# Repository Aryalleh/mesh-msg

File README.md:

# Mava (mesh-msg)

English | [فارسی](README.fa.md)

An off-grid, censorship-resistant messenger built as a **mesh of meshes**.

Messages travel over whatever path exists:

| Tier | Transport | Range | Payload |
|---|---|---|---|
| 0 — Local | BLE, Wi-Fi Direct, Wi-Fi Aware (phone ↔ phone) | 10–100 m per hop | Text + small media |
| 1 — LoRa | LoRa nodes **broadcast**: gateway nodes take packets from a relay and broadcast them to every node in range — offline users, or other relays with no connection to the origin | 2–15 km per hop | Text only (~200 B packets) |
| 2a — Regional | Phones/PCs on a country's domestic network → in-region relay | One country, even during an international blackout | Anything |
| 2b — Global | Federated relays (EU, US, Asia, AU); regions joined by volunteer **bridges** (VPN, Starlink, unfiltered SIM) | Global | Anything |

Chats are one-to-one, **private groups** (a member list: each message goes to every member separately, with ✓✓ per member), **regional public chats**
(one per city or country name, e.g. `#tehran`) and one **global public chat** (`#global`).
All of them travel over every tier above (the global chat skips LoRa to save airtime).

Any phone or PC that can reach a relay can register as a **gateway** ("I'm online — send me
traffic for the mesh around me"). Clients: Android, and desktop (Linux first, then Windows
and macOS).

The relay list updates itself: apps ship the official list ([network/relays.json](network/relays.json),
starting with the original relay eu-1), refresh it, learn relays from other relays, and pass the
relay they use to nearby phones, PCs and LoRa nodes, so a new relay spreads through the mesh even
where the old one is blocked. Each relay is checked before use.

```
   City A                          ~10 km                         City B
 ┌──────────────────┐                                    ┌──────────────────┐
 │ 📱──BLE──📱──📱   │      LoRa backbone (rooftops)      │   📱──📱──BLE──📱 │
 │      📱──BLE──📡──┼────────────────────────────────────┼──📡──BLE──📱      │
 │  (has VPN) 📱     │                                    │     📱 (online)   │
 └───────┼──────────┘                                    └───────┼──────────┘
         └──────────── Internet relay servers (Tier 2) ──────────┘
```

## Core principles

- **Delay-tolerant / store-and-forward** — nodes hold encrypted messages until a better route appears.
- **Identity = public key** — no phone numbers, no accounts.
- **End-to-end encryption above every transport** — relays, LoRa nodes and servers carry only ciphertext. No custom crypto.
- **Transport-agnostic routing** — each tier is just an interface; pick the cheapest one that works.
- **Survives server loss** — Tier 2 is optional; Tiers 0 and 1 work without any internet.
- **Photos, voice and video messages, files** — sent apart from messages so chats never lag: phone to phone over Bluetooth/Wi-Fi/direct internet links (both online). Files marked *important* also go through a relay and reach someone who is offline, a few per day per user. Never over LoRa.

## Threat model highlights

Designed with internet shutdowns (e.g. Iran) in mind: radio direction-finding, device seizure,
blocked servers, no app-store access. See [docs/threat-model.md](docs/threat-model.md).

## Design docs

- [Architecture](docs/architecture.md) — tiers, components, message path
- [Protocol](docs/protocol.md) — identity, packet format, encryption, routing
- [Core](docs/core.md) — shared Go core (protocol, crypto, router)
- [Server](docs/server.md) — regional & global relays, gateways, bridges
- [Desktop](docs/desktop.md) — `meshd` client / gateway / bridge (Linux first)
- [Android](docs/android.md) — app, phone-to-phone mesh
- [Firmware](docs/firmware.md) — LoRa node hardware framework
- [Threat model](docs/threat-model.md)
- [Decisions](docs/decisions.md) · [Roadmap](docs/roadmap.md)

## Status

M0–M3 implemented: Go core, simulator, relay and Linux desktop (`meshd` + `mesh`),
with language-neutral test vectors. M4 (LoRa firmware): the whole node
(protocol, router, MAC, store, host link) is board-independent and host-tested against the same
vectors (`make -C firmware test`); `scripts/e2e-lora.sh` sends a text PC → node → repeater →
node → PC with real firmware nodes on a simulated radio; PlatformIO builds for Heltec V3,
T-Beam S3, RAK4631 and T-Echo exist but are not yet verified on hardware. M5 (Android): the core is bound with gomobile
(`mobile/`), and `android/` has the app — Compose UI in Persian and English, BLE mesh
transport, USB LoRa link, foreground service — built and tested on the JVM, not yet on phones.
See [roadmap](docs/roadmap.md).

## Layout

```
docs/        design docs
spec/        protocol test vectors
core/        shared Go core: protocol, crypto, router, store, relay client
server/      relay server (Go)
desktop/     meshd daemon + CLI + web UI (Go; Linux first)
android/     Android app (Kotlin + Go core via gomobile)
firmware/    LoRa node firmware (C++ / PlatformIO)
sim/         network simulator (Go, uses core/)
```

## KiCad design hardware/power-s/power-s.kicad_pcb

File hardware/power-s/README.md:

# Model S power board

The power section of the Model S handheld (docs/handheld.md §1–2) as its own 2-layer board
inside the case, plugged into the 2-layer main board. Everything here is **generated**: change
the scripts, not the KiCad files.

| | |
|---|---|
| Size | 54 × 36 mm, 2 layers, 1.6 mm, all parts on top, 4 × M2 holes |
| Input | USB-C (5 V sink, CC 5.1 k, USBLC6 on D+/D−, SMF5.0A on VBUS) |
| Battery | 1-cell LiPo with 10 k NTC on JST-PH 3-pin (1 = BAT+, 2 = NTC, 3 = BAT−) |
| PMU | X-Powers AXP2101: linear charger ≤ 1 A, power path, fuel gauge, DCDC1 + 6 LDOs |
| RTC | NXP PCF85063A from the battery through a TI TPS7A02 (25 nA) |
| To main board | J3, 2 × 14 1.27 mm SMD header (mates with a 2 × 14 1.27 mm SMD socket) |

## Rails

| Rail | Source | Max | Model S load | J3 pins |
|---|---|---|---|---|
| VBAT | battery | – | NS4150B, motor, LTE board (2 A peaks) | 1–4 |
| VSYS | AXP2101 power path | 2 A total | spare for loads that must run from USB without a battery | 7–8 |
| +3V3 | DCDC1 | 2 A | ESP32-S3, flash, PSRAM | 11–13 |
| 3V3_LORA | ALDO2 | 300 mA | SX1262 module | 15 |
| 3V3_AUDIO | ALDO3 | 300 mA | ES8388 | 16 |
| 3V3_SD | ALDO4 | 300 mA | microSD | 17 |
| 3V3_LCD | BLDO1 | 300 mA | screen VCI, touch | 18 |
| 3V3_GPS | BLDO2 | 300 mA | GPS / LTE option (J6 VCC, LTE load-switch enable) | 19 |
| VSPARE | ALDO1 | 300 mA | spare, off by default | 20 |
| VRTC | TPS7A02 from VBAT | 200 mA | PCF85063A only | – |

GND on J3 pins 5, 6, 9, 10, 14, 21. Header pins carry 1 A each.

## Signals to the ESP32-S3

| J3 | Net | ESP32-S3 | |
|---|---|---|---|
| 23 / 24 | I2C_SDA / I2C_SCL | GPIO18 / GPIO8 | AXP2101 at 0x34, PCF85063A at 0x51; 2.2 k pull-ups on this board |
| 25 | PMU_IRQ | GPIO2 | open drain, 10 k pull-up here; AXP2101 IRQ and RTC INT wired together |
| 26 | PMU_PWROK | (EN, optional) | high once the rails are up |
| 22 | PWR_KEY | – | side power key on the main board, to GND (parallel to SW1 here) |
| 27 / 28 | USB_D_P / USB_D_N | GPIO20 / GPIO19 | native USB, ESD-protected at the connector |

**Charge status and battery capacity** reach the ESP32-S3 over I2C, nothing else is needed:
the AXP2101's fuel gauge (E-Gauge) gives the state of charge in % (REG A4h), the battery
voltage and charge current from its ADC, and the charger state (charging / full / discharging,
VBUS present) in its status registers. PMU_IRQ goes low on every change (USB in/out, charge
start/done, battery low, power key), so the ESP32-S3 sleeps until something happens.
For an accurate percentage the firmware loads the battery's 128-byte model into the gauge at
start-up (X-Powers design guide §6); without it the gauge uses its generic curve.
XPowersLib (already used in `firmware/`) has the register map.

## Firmware duties

- Set each rail's voltage and enable it before use; rails start from the AXP2101's eFuse
  defaults.
- Charge current ≤ 1 A for the 2500 mAh pack (REG 62h), target 4.2 V (REG 64h).
- TS pin: the pack's 10 k NTC; for a pack without NTC fit R10 (10 k, DNP) or turn TS off.
- PCF85063A: CAP_SEL = 12.5 pF, CLKOUT off (COF = 111).

## Files

| File | |
|---|---|
| `generate_schematic.py` | the schematic (spec + drawing; `verify()` proves they match) |
| `place_board.py` | placement |
| `route_board.py` | routing: power paths scripted, the rest Freerouting, stored in `routing/` |
| `make_rails.py` | power symbols for this board's rails (`lib/rails.kicad_sym`) |
| `lib/` | AXP2101, TPS7A02, PCF85063ATT, inductor: symbols/footprints from LCSC (easyeda2kicad) |
| `kicad-env.sh` | KiCad 10 from the AppImage (`kicad-cli`, `kpy` = KiCad's Python) |
| `schlib.py`, `pcblib.py`, `routelib.py`, `subcircuits.py`, `jlc_cpl.py` | the libraries the scripts use |

Regenerate:

```
. ./kicad-env.sh
python3 make_rails.py
python3 generate_schematic.py --force --render
kpy place_board.py --force
kpy route_board.py
```

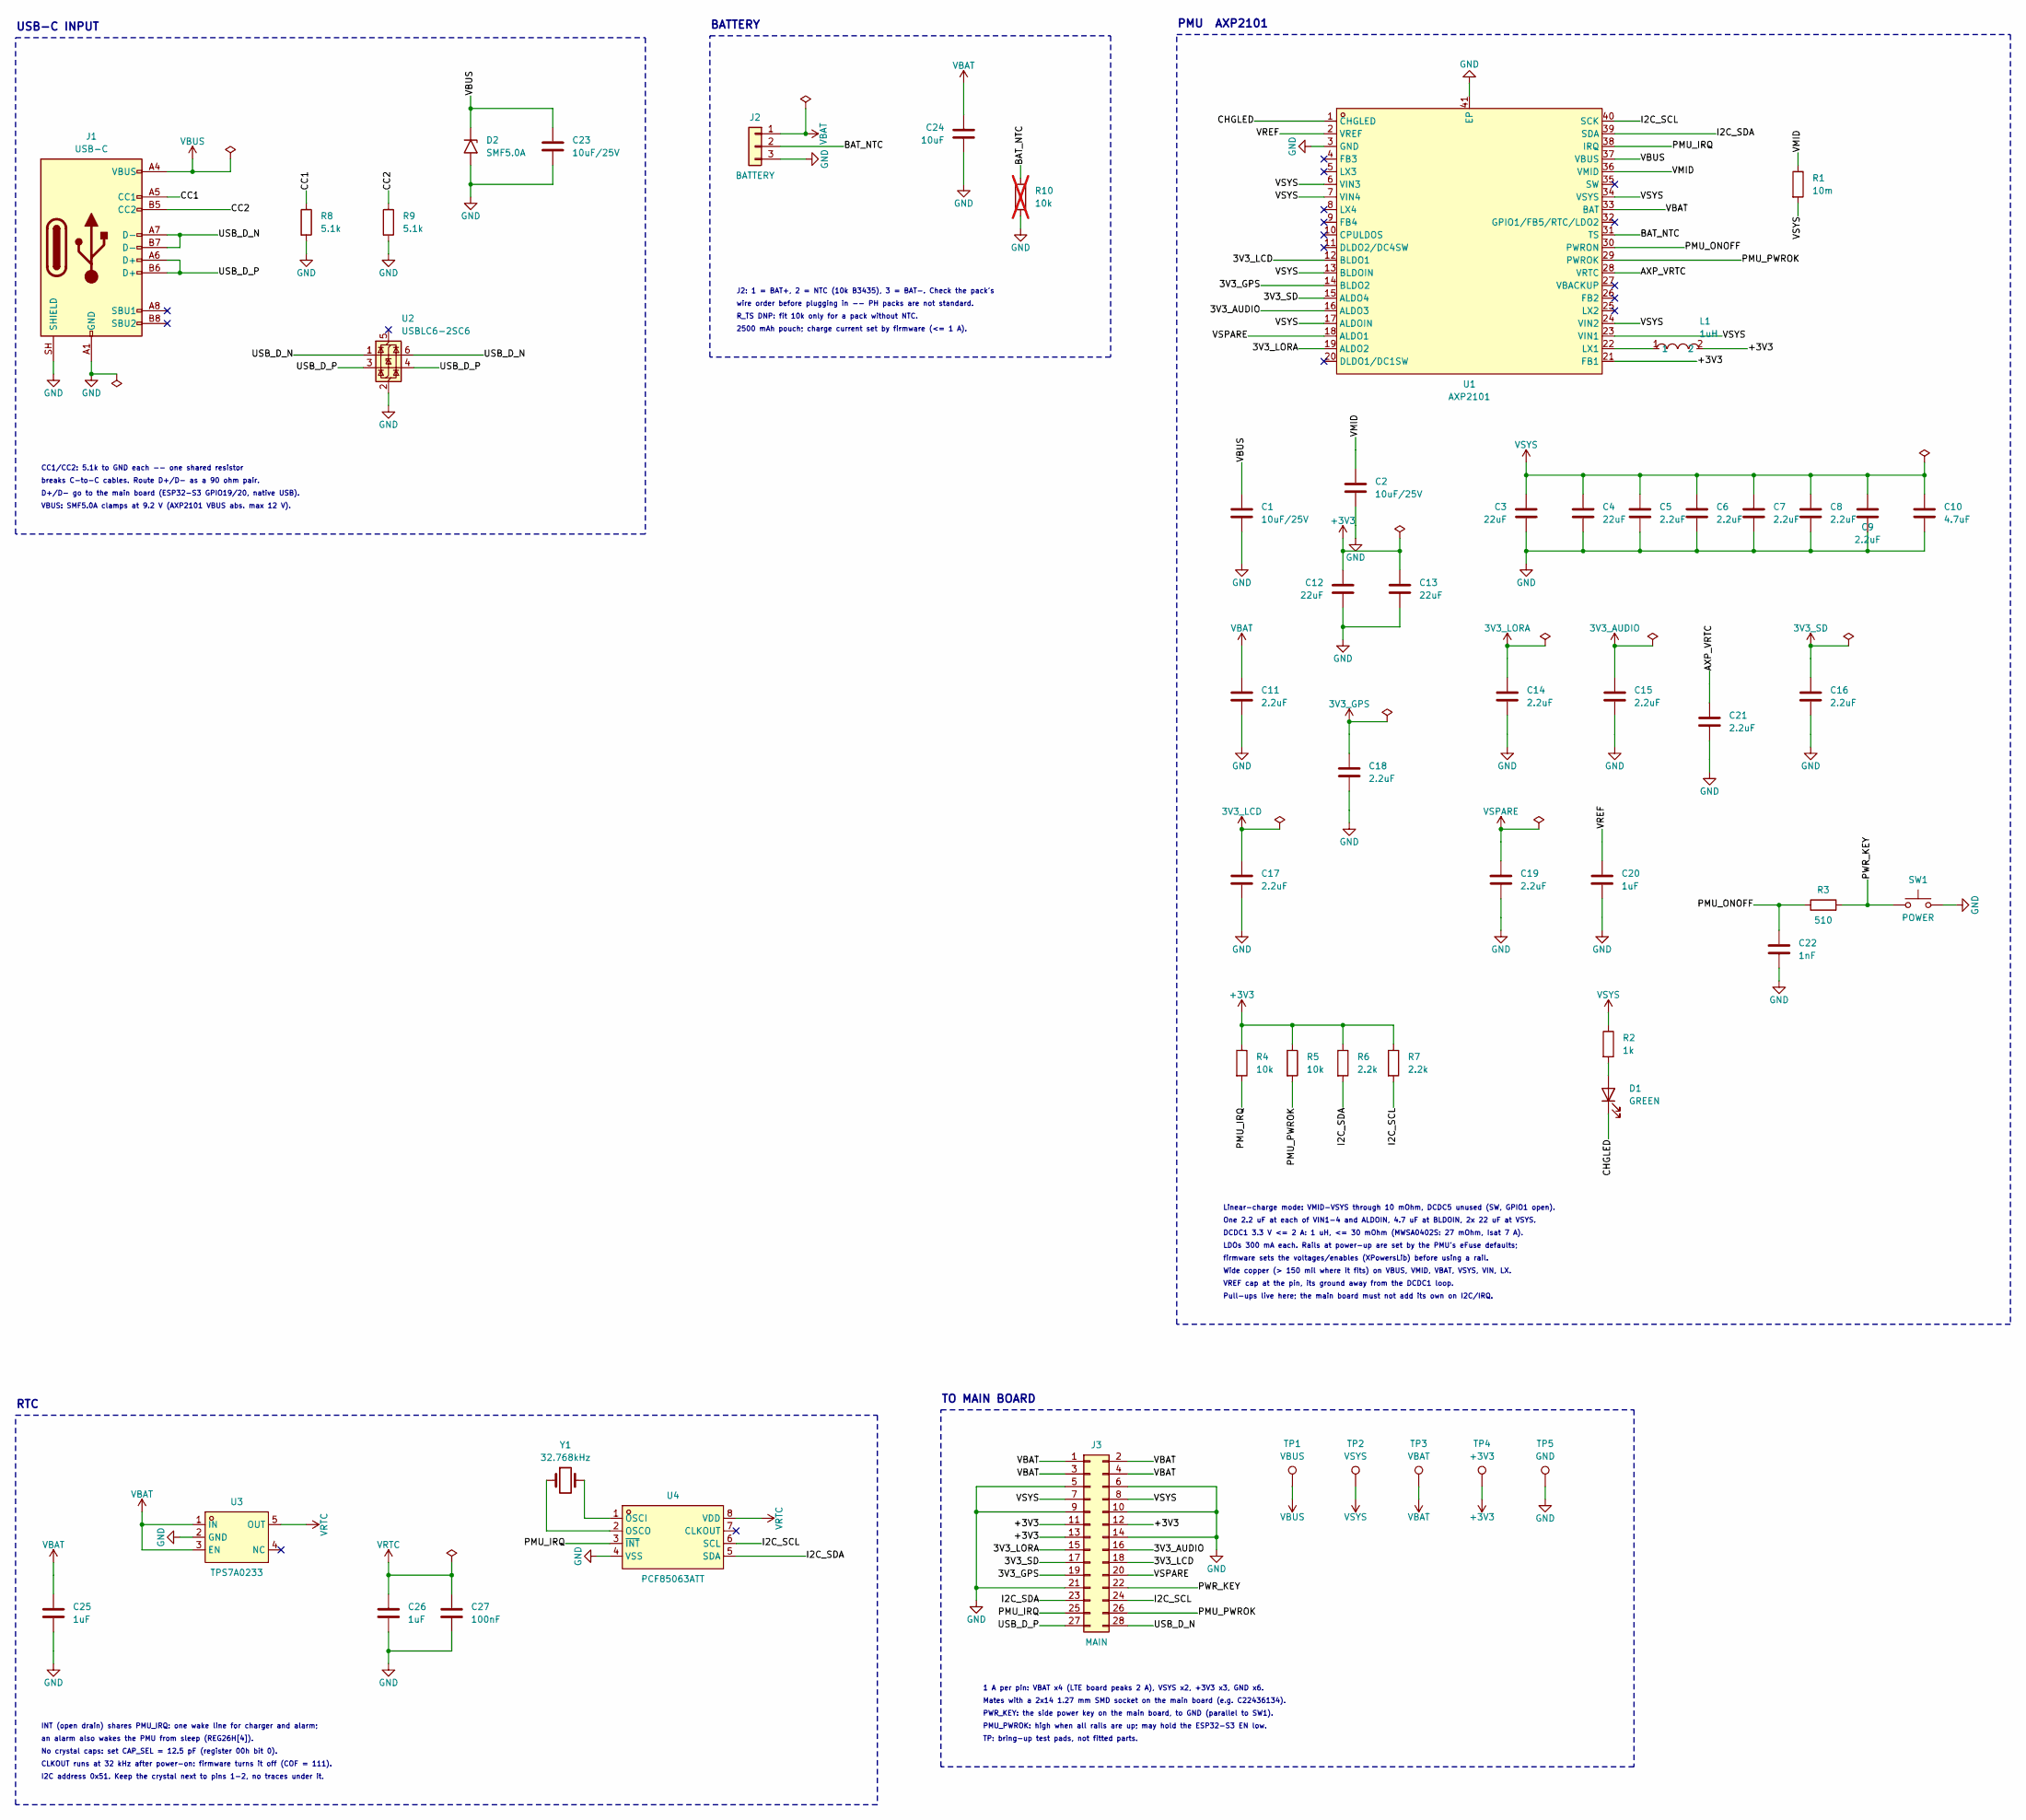
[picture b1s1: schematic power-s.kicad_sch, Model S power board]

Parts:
C1, C2, C23: 10uF/25V; C_0805_2012Metric; MPN CL21A106KAYNNNE; LCSC C15850
C3, C4, C12, C13: 22uF; C_0805_2012Metric; MPN CL21A226MAQNNNE; LCSC C45783
C5, C6, C7, C8, C9, C11, C14, C15, C16, C17, C18, C19, C21: 2.2uF; C_0402_1005Metric; MPN CL05A225MQ5NSNC; LCSC C12530
C10: 4.7uF; C_0603_1608Metric; MPN CL10A475KO8NNNC; LCSC C19666
C20, C25, C26: 1uF; C_0402_1005Metric; MPN CL05A105KA5NQNC; LCSC C52923
C22: 1nF; C_0402_1005Metric; MPN 0402B102K500NT; LCSC C1523
C24: 10uF; C_0603_1608Metric; MPN CL10A106KP8NNNC; LCSC C19702
C27: 100nF; C_0402_1005Metric; MPN CL05B104KO5NNNC; LCSC C1525
D1: GREEN; LED_0603_1608Metric; MPN 19-217/GHC-YR1S2/6T; LCSC C2986059
D2: SMF5.0A; D_SOD-123F; MPN SMF5.0A; LCSC C193402
J1: USB-C; USB_C_Receptacle_HRO_TYPE-C-31-M-12; MPN TYPE-C-31-M-12; LCSC C165948
J2: BATTERY; JST_PH_S3B-PH-SM4-TB_1x03-1MP_P2.00mm_Horizontal; MPN S3B-PH-SM4-TB(LF)(SN); LCSC C265101
J3: MAIN; PinHeader_2x14_P1.27mm_Vertical_SMD; MPN LCK-PH19-12728PC40D55-G1WT0; LCSC C54950782
L1: 1uH; IND-SMD_L4.4-W4.2; MPN MWSA0402S-1R0MT; LCSC C408332
R1: 10m; R_1206_3216Metric; MPN FMF06FTHR010-LH; LCSC C105362
R2: 1k; R_0402_1005Metric; MPN 0402WGF1001TCE; LCSC C11702
R3: 510; R_0402_1005Metric; MPN 0402WGF5100TCE; LCSC C25123
R4, R5: 10k; R_0402_1005Metric; MPN 0402WGF1002TCE; LCSC C25744
R6, R7: 2.2k; R_0402_1005Metric; MPN 0402WGF2201TCE; LCSC C25879
R8, R9: 5.1k; R_0402_1005Metric; MPN 0402WGF5101TCE; LCSC C25905
R10: 10k; R_0402_1005Metric; MPN 0402WGF1002TCE; LCSC C25744; not fitted
SW1: POWER; SW_Push_1P1T_XKB_TS-1187A; MPN TS-1187A-B-A-B; LCSC C318884
TP1: VBUS; TestPoint_Pad_D1.0mm
TP2: VSYS; TestPoint_Pad_D1.0mm
TP3: VBAT; TestPoint_Pad_D1.0mm
TP4: +3V3; TestPoint_Pad_D1.0mm
TP5: GND; TestPoint_Pad_D1.0mm
U1: AXP2101; QFN-40_L5.0-W5.0-P0.40-TL-EP3.4; MPN AXP2101; LCSC C3036461
U2: USBLC6-2SC6; SOT-23-6; MPN USBLC6-2SC6; LCSC C7519
U3: TPS7A0233; SOT-23-5_L2.9-W1.6-P0.95-LS2.8-BR; MPN TPS7A0233PDBVR; LCSC C2887324
U4: PCF85063ATT; TSSOP-8_L3.0-W3.0-P0.65-LS4.9-BL; MPN PCF85063ATT/AJ; LCSC C165608
Y1: 32.768kHz; Crystal_SMD_3215-2Pin_3.2x1.5mm; MPN SC-32S 32.768kHz 20PPM 12.5pF; LCSC C97606

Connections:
/AXP_VRTC: C21.1, U1.28 (VRTC)
/BAT_NTC: J2.2, R10.1, U1.31 (TS)
/CC1: J1.A5 (CC1), R8.1
/CC2: J1.B5 (CC2), R9.1
/CHGLED: D1.1 (K), U1.1 (CHGLED)
/I2C_SCL: J3.24, R7.2, U1.40 (SCK), U4.6 (SCL)
/I2C_SDA: J3.23, R6.2, U1.39 (SDA), U4.5 (SDA)
/PMU_IRQ: J3.25, R4.2, U1.38 (IRQ), U4.3 (~INT)
/PMU_ONOFF: C22.1, R3.1, U1.30 (PWRON)
/PMU_PWROK: J3.26, R5.2, U1.29 (PWROK)
/PWR_KEY: J3.22, R3.2, SW1.1
/USB_D_N: J1.A7 (D-), J1.B7 (D-), J3.28, U2.1 (I/O1), U2.6 (I/O1)
/USB_D_P: J1.A6 (D+), J1.B6 (D+), J3.27, U2.3 (I/O2), U2.4 (I/O2)
/VMID: C2.1, R1.1, U1.36 (VMID)
/VREF: C20.1, U1.2 (VREF)
unnamed: D1.2 (A), R2.2
unnamed: L1.1, U1.22 (LX1)
unnamed: U4.1 (OSCI), Y1.2
unnamed: U4.2 (OSCO), Y1.1

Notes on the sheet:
INT (open drain) shares PMU_IRQ: one wake line for charger and alarm;
RTC
I2C address 0x51. Keep the crystal next to pins 1-2, no traces under it.
Wide copper (> 150 mil where it fits) on VBUS, VMID, VBAT, VSYS, VIN, LX.
TP: bring-up test pads, not fitted parts.
D+/D- go to the main board (ESP32-S3 GPIO19/20, native USB).
wire order before plugging in -- PH packs are not standard.
1 A per pin: VBAT x4 (LTE board peaks 2 A), VSYS x2, +3V3 x3, GND x6.
One 2.2 uF at each of VIN1-4 and ALDOIN, 4.7 uF at BLDOIN, 2x 22 uF at VSYS.
2500 mAh pouch; charge current set by firmware (<= 1 A).
TO MAIN BOARD
J2: 1 = BAT+, 2 = NTC (10k B3435), 3 = BAT-. Check the pack's
VBUS: SMF5.0A clamps at 9.2 V (AXP2101 VBUS abs. max 12 V).
USB-C INPUT
Pull-ups live here; the main board must not add its own on I2C/IRQ.
No crystal caps: set CAP_SEL = 12.5 pF (register 00h bit 0).
PWR_KEY: the side power key on the main board, to GND (parallel to SW1).
VREF cap at the pin, its ground away from the DCDC1 loop.
PMU_PWROK: high when all rails are up; may hold the ESP32-S3 EN low.
LDOs 300 mA each. Rails at power-up are set by the PMU's eFuse defaults;
firmware sets the voltages/enables (XPowersLib) before using a rail.
an alarm also wakes the PMU from sleep (REG26H[4]).
Mates with a 2x14 1.27 mm SMD socket on the main board (e.g. C22436134).
PMU AXP2101
breaks C-to-C cables. Route D+/D- as a 90 ohm pair.
CLKOUT runs at 32 kHz after power-on: firmware turns it off (COF = 111).
CC1/CC2: 5.1k to GND each -- one shared resistor
R_TS DNP: fit 10k only for a pack without NTC.
DCDC1 3.3 V <= 2 A: 1 uH, <= 30 mOhm (MWSA0402S: 27 mOhm, Isat 7 A).
Linear-charge mode: VMID-VSYS through 10 mOhm, DCDC5 unused (SW, GPIO1 open).
BATTERY

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
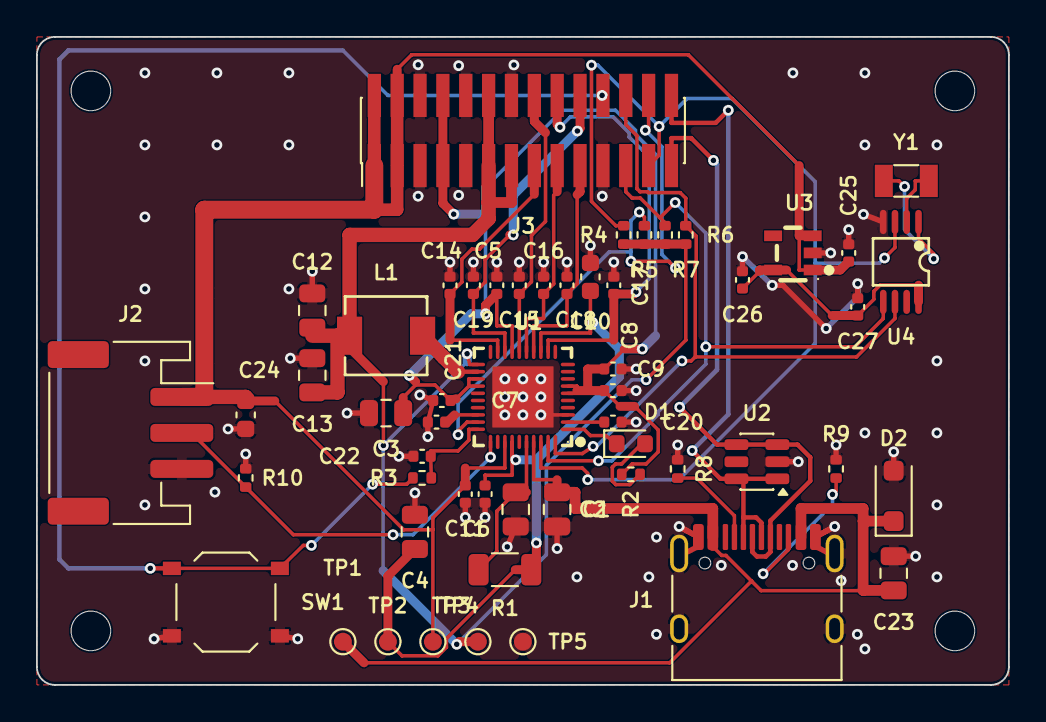
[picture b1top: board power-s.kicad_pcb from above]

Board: 2 copper layers, 54.0 x 36.0 mm, 58 parts (0 on the bottom side), 31 nets.

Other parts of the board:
H1, H2, H3, H4: MountingHole_2.2mm

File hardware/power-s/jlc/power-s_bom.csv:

Comment,Designator,Footprint,LCSC
10uF/25V,"C1,C2,C23",C_0805_2012Metric,C15850
4.7uF,C10,C_0603_1608Metric,C19666
1uF,"C20,C25,C26",C_0402_1005Metric,C52923
1nF,C22,C_0402_1005Metric,C1523
10uF,C24,C_0603_1608Metric,C19702
100nF,C27,C_0402_1005Metric,C1525
22uF,"C3,C4,C12,C13",C_0805_2012Metric,C45783
2.2uF,"C5,C6,C7,C8,C9,C11,C14,C15,C16,C17,C18,C19,C21",C_0402_1005Metric,C12530
GREEN,D1,LED_0603_1608Metric,C2986059
SMF5.0A,D2,D_SOD-123F,C193402
USB-C,J1,USB_C_Receptacle_HRO_TYPE-C-31-M-12,C165948
BATTERY,J2,JST_PH_S3B-PH-SM4-TB_1x03-1MP_P2.00mm_Horizontal,C265101
MAIN,J3,PinHeader_2x14_P1.27mm_Vertical_SMD,C54950782
1uH,L1,IND-SMD_L4.4-W4.2,C408332
10m,R1,R_1206_3216Metric,C105362
1k,R2,R_0402_1005Metric,C11702
510,R3,R_0402_1005Metric,C25123
10k,"R4,R5",R_0402_1005Metric,C25744
2.2k,"R6,R7",R_0402_1005Metric,C25879
5.1k,"R8,R9",R_0402_1005Metric,C25905
POWER,SW1,SW_Push_1P1T_XKB_TS-1187A,C318884
AXP2101,U1,QFN-40_L5.0-W5.0-P0.40-TL-EP3.4,C3036461
USBLC6-2SC6,U2,SOT-23-6,C7519
TPS7A0233,U3,SOT-23-5_L2.9-W1.6-P0.95-LS2.8-BR,C2887324
PCF85063ATT,U4,TSSOP-8_L3.0-W3.0-P0.65-LS4.9-BL,C165608
32.768kHz,Y1,Crystal_SMD_3215-2Pin_3.2x1.5mm,C97606

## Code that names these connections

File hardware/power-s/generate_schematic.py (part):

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  + 6 LDOs for the Model S rails) -> 2x14 1.27 mm board-to-board header to the
  main board. RTC (PCF85063A) on the battery through a 25 nA LDO (TPS7A02).
  Charge state reaches the ESP32-S3 over I2C (AXP2101 status/fuel-gauge
  registers) and PMU_IRQ (GPIO2), which fires on every charger event.

AXP2101 circuit = X-Powers "AXP2101 design guide V1.0" §3.2 (linear-charge
mode) and datasheet V1.4 table 4-1; pin numbers checked against both.
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        self.put(s, self.j, x, y, mirror="y")
        p1, p2, p3 = (s.pin(self.j, n) for n in ("1", "2", "3"))
        s.stub(self.j, "1", 5.08, power="rails:VBAT")
        s.stub(self.j, "2", 12.7, label="BAT_NTC")
        g = s.stub(self.j, "3", 5.08, power="GND")
        # PWR_FLAG: VBAT and the battery's GND enter the board here
        top = (p1[0] + 5.08, p1[1])
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                    place=lambda r, xx, yy: self.put(s, r, xx, yy))
        self.put(s, self.rts, snap(x + 22.86), snap(y + 10.16))
        s._sym(self.rts)[0]["dnp"] = True
        s.stub(self.rts, 1, 2.54, label="BAT_NTC")
        s.stub(self.rts, 2, 2.54, power="GND")


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            self.banks.append((rail, refs_, kind))

        bank("VBUS", ["10uF/25V"])
        bank("VMID", ["10uF/25V"], "label")
        bank("VSYS", ["22uF", "22uF", "2.2uF", "2.2uF", "2.2uF", "2.2uF", "2.2uF", "4.7uF"])
        bank("VBAT", ["2.2uF"])
        bank("+3V3", ["22uF", "22uF"])
        for rail in ("3V3_LORA", "3V3_AUDIO", "3V3_SD", "3V3_LCD", "3V3_GPS", "VSPARE"):
            bank(rail, ["2.2uF"])
        bank("VREF", ["1uF"], "label")
        bank("AXP_VRTC", ["2.2uF"], "label")

        # charge LED: VSYS -> 1k -> LED -> CHGLED (guide §4.3 item 2)
        self.rled = P("R", RES["1k"])
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            self.pull.append(r)

        self.notes = [
            "Linear-charge mode: VMID-VSYS through 10 mOhm, DCDC5 unused (SW, GPIO1 open).",
            "One 2.2 uF at each of VIN1-4 and ALDOIN, 4.7 uF at BLDOIN, 2x 22 uF at VSYS.",
            "DCDC1 3.3 V <= 2 A: 1 uH, <= 30 mOhm (MWSA0402S: 27 mOhm, Isat 7 A).",
            "LDOs 300 mA each. Rails at power-up are set by the PMU's eFuse defaults;",
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        # VMID -> 10 mOhm -> VSYS, beside the right flank
        rx, ry = snap(x + 58.42), snap(y - 10.16)
        self.put(s, self.rmid, rx, ry)
        s.stub(self.rmid, 1, 2.54, label="VMID")
        s.stub(self.rmid, 2, 2.54, label="VSYS")

        # capacitor banks in rows below the IC
        bx0, by = snap(x - 45.72), snap(y + 45.72)
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        s.stub(self.rled, 1, 2.54, power="rails:VSYS")
        self.put(s, self.led, lx0, snap(py + 10.16), rot=90)
        s.wire(s.pin(self.rled, 2), s.pin(self.led, 2))
        s.stub(self.led, 1, 5.08, label="CHGLED")

        # power key: PWRON label, 1nF down to GND, 510R across to PWR_KEY, key to GND
        kx = snap(bx0 + 81.28)
        self.put(s, self.ckey, kx, snap(py + 7.62))
        s.stub(self.ckey, 2, 2.54, power="GND")
        top = s.pin(self.ckey, 1)
        n = (top[0], snap(top[1] - 5.08))                  # PMU_ONOFF node
        s.wire(top, n, (n[0] - 5.08, n[1]))
        s.label("PMU_ONOFF", n[0] - 5.08, n[1], angle=180)
        # 510R horizontal, pin 1 on the left (rot 90 turns pin 1 to the left)
        self.put_pin(s, self.rkey, 1, (snap(n[0] + 5.08), n[1]), rot=90)
        s.wire(n, s.pin(self.rkey, 1))
        k = (snap(s.pin(self.rkey, 2)[0] + 5.08), n[1])    # PWR_KEY node
        s.wire(s.pin(self.rkey, 2), k)
        s.wire(k, (k[0], snap(k[1] - 5.08)))
        s.label("PWR_KEY", k[0], snap(k[1] - 5.08), angle=90)
        self.put_pin(s, self.sw, 1, (snap(k[0] + 5.08), k[1]))
        s.wire(k, s.pin(self.sw, 1))
        s.stub(self.sw, 2, 2.54, power="GND")
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        self.put(s, r, snap(x + 76.2), y)
        s.stub(r, "8", 5.08, power="rails:VRTC")
        s.stub(r, "4", 2.54, power="GND")
        s.stub(r, "3", 5.08, label="PMU_IRQ")
        s.stub(r, "5", 5.08, label="I2C_SDA")
        s.stub(r, "6", 5.08, label="I2C_SCL")
        s.nc(r, "7")
        # crystal above-left of the RTC: OSCI and OSCO each one clean L, no crossing
        o1, o2 = s.pin(r, "1"), s.pin(r, "2")
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                                  "", "", ""))
            self.conn(net, (tp, 1))
            self.tps.append((tp, net))
        self.notes = ["1 A per pin: VBAT x4 (LTE board peaks 2 A), VSYS x2, +3V3 x3, GND x6.",
                      "Mates with a 2x14 1.27 mm SMD socket on the main board (e.g. C22436134).",
                      "PWR_KEY: the side power key on the main board, to GND (parallel to SW1).",
                      "PMU_PWROK: high when all rails are up; may hold the ESP32-S3 EN low.",
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
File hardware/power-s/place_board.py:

"""Model S power board -- placement.

    . ./kicad-env.sh && kpy place_board.py [--force]

Board mm, origin top-left, Y down. Re-running resets every part listed here
to its table position (parts locked in KiCad are not touched by this script
only if you remove them from the table first).

Mechanics (README.md): 54 x 36 mm, 2 layers, all parts on top. Top edge faces
the main board (2x14 1.27 mm header J3, mezzanine), USB-C on the bottom edge,
battery JST-PH on the left edge, 4x M2 holes in the corners.
"""
import os
import sys

HERE = os.path.dirname(os.path.abspath(__file__))
sys.path.insert(0, HERE)
import pcblib                                     # noqa: E402
from pcblib import Board                          # noqa: E402

NAME = "power-s"
W, H = 54.0, 36.0          # case inside is ~58 mm wide (docs/handheld.md: 62 mm outside)

# Pad orientation used below: a two-pad part at rot 0 has pad 1 on the left,
# rot 90 pad 1 at the bottom, rot 180 on the right, rot 270 at the top.
# Every capacitor's pad 1 is its rail, pad 2 ground, so the rot puts the rail
# pad toward the pin it serves.
#
# AXP2101 rotated 180 deg (pad positions at (27, 20)):
#   top    y 17.5  LDO outputs and their inputs, pins 19..12 at x 25.6..28.4
#   left   x 24.5  FB1 18.2, LX1 18.6, VIN1/2 19.0/19.4, VRTC 21.0, PWROK 21.4, PWRON 21.8
#   bottom y 22.5  TS 25.2, BAT 26.0, VSYS 26.4, VMID 27.2, VBUS 27.6, IRQ/SDA/SCL 28.0..28.8
#   right  x 29.5  VIN3/4 19.4/19.8, GND 21.0, VREF 21.4, CHGLED 21.8
U1 = (27.0, 20.0)

PLACEMENT = {
    # ref: (x, y, rot)
    "U1": (U1[0], U1[1], 180),
    "J3": (27.0, 5.2, 90),            # to the main board, along the top edge
    # DCDC1: LX1 -> L1 -> +3V3, output caps beside L1, VIN1/2 caps under it
    "L1": (19.4, 16.6, 0),            # pad 1 (LX) on the right, facing pin 22
    "C12": (15.3, 15.2, 90),
    "C13": (15.3, 18.8, 90),
    "C7": (22.5, 20.2, 180),          # VIN1/2 2.2 uF at the pins
    "C3": (19.4, 20.9, 180),          # VIN1/2 22 uF
    "C21": (22.2, 21.4, 180),         # VRTC (pin 28)
    "C22": (21.4, 23.3, 180),           # PWRON 1 nF
    "R3": (21.4, 24.5, 180),            # PWRON 510 R to the key
    # top row: LDO outputs and ALDOIN/BLDOIN, in pin order, rail pad down, 1.3 mm pitch:
    # route_board.py fans the 0.4 mm pins out to them in a staircase
    "C14": (22.95, 13.8, 90),          # 3V3_LORA   pin 19
    "C19": (24.25, 13.8, 90),          # VSPARE     pin 18
    "C5": (25.55, 13.8, 90),           # ALDOIN     pin 17
    "C15": (26.8, 13.8, 90),          # 3V3_AUDIO  pin 16
    "C16": (28.15, 13.8, 90),          # 3V3_SD     pin 15
    "C18": (29.45, 13.8, 90),          # 3V3_GPS    pin 14
    "C10": (30.75, 13.335, 90),          # BLDOIN 4.7 uF pin 13
    "C17": (32.05, 13.8, 90),         # 3V3_LCD    pin 12
    # right: VIN3/4, VREF, charge LED
    "C9": (32.0, 18.45, 0),
    "C8": (32.0, 19.65, 0),
    "C20": (32.0, 21.4, 0),          # VREF 1 uF at the pin
    "D1": (33.0, 22.6, 0),            # CHGLED sinks: cathode (pad 1) toward U1
    "R2": (33.0, 24.3, 0),
    # bottom: BAT, VSYS, VMID, VBUS, the 10 mOhm VMID->VSYS link, VSYS bulk
    "C11": (23.8, 25.4, 270),         # BAT 2.2 uF
    "C6": (24.9, 25.4, 270),          # VSYS 2.2 uF pin 34
    "C2": (26.6, 26.25, 270),         # VMID 10 uF
    "C1": (28.9, 26.25, 270),         # VBUS 10 uF (I2C leaves above it)
    "R1": (26.0, 29.6, 0),
    "C4": (21.0, 27.5, 90),           # VSYS 22 uF bulk
    # I2C / IRQ / PWROK pull-ups to +3V3, under the header's signal pins
    "R4": (32.6, 11.0, 90),
    "R5": (33.75, 11.0, 90),
    "R6": (34.9, 11.0, 90),
    "R7": (36.05, 11.0, 90),
    # USB-C on the bottom edge, right: D+/D- run up the free right side to
    # J3 27/28; ESD flow-through right above the receptacle
    "J1": (40.0, H - 4.17, 0),
    "U2": (40.0, 23.6, 180),
    "R8": (35.6, 24.0, 90),
    "R9": (44.4, 24.0, 90),
    "D2": (47.6, 25.5, 90),
    "C23": (47.6, 29.8, 90),
    # battery on the left edge, cable leaves to the left; VBAT is one short
    # run to J3 pins 1-4 (the header's left end) and to BAT (pin 33)
    "J2": (5.2, 22.0, 270),
    "C24": (11.6, 21.0, 270),         # VBAT pad up, in line with J2 pin 1
    "R10": (11.6, 24.5, 90),
    # RTC, top right
    "U3": (42.0, 12.0, 0),
    "C25": (45.1, 12.0, 90),
    "C26": (39.2, 13.5, 90),
    "U4": (48.0, 12.5, 180),
    "Y1": (48.3, 8.0, 0),
    "C27": (45.6, 15.0, 90),
    # power key (bench; the case key is on the main board, PWR_KEY on J3)
    "SW1": (10.5, 31.4, 0),
    # test pads along the bottom edge
    "TP1": (17.0, 33.6, 0),
    "TP2": (19.5, 33.6, 0),
    "TP3": (22.0, 33.6, 0),
    "TP4": (24.5, 33.6, 0),
    "TP5": (27.0, 33.6, 0),
}
HOLES = [(3.0, 3.0), (W - 3.0, 3.0), (3.0, H - 3.0), (W - 3.0, H - 3.0)]


def main():
    pcblib.create_board(__file__, NAME, layers=2)
    b = Board(__file__, NAME, size=(W, H))
    b.sync_footprints(prune=True)
    b.refresh_footprints()                          # pick up lib/ fixes (fix_footprints.py)
    b.outline(radius=1.0)
    b.place_all(PLACEMENT)
    b.link_schematic()
    # match the symbols: test pads on the BOM (no LCSC, so not on the JLC BOM), R10 not fitted
    for ref, fp in b.fps.items():
        if ref.startswith("TP"):
            fp.SetExcludedFromBOM(False)    # symbols are on the BOM; jlc_cpl skips parts without LCSC
    b.fps["R10"].SetDNP(True)
    for x, y in HOLES:
        b.hole(x, y, 2.2)
    b.tidy_references()
    try:
        b.check()
    except SystemExit:
        if "--preview" not in sys.argv:
            raise
        print("  (--preview: saving and rendering despite check errors)")
    b.save(force="--force" in sys.argv or "--preview" in sys.argv)
    b.drc()
    b.render(os.path.join(HERE, "out", "pcb"), views=("top",))   # angled 3D takes >10 min here


if __name__ == "__main__":
    main()
